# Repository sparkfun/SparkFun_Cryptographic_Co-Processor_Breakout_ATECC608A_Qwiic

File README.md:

SparkFun Cryptographic Co-Processor Breakout - ATECC608A (Qwiic)
========================================

[*SparkFun Cryptographic Co-Processor Breakout - ATECC608A (Qwiic) (DEV-15573)*](https://www.sparkfun.com/products/18077)

The SparkFun ATECC608A Cryptographic Co-processor Breakout allows you to add strong security to your IoT node, edge device, or embedded system. This includes asymmetric authentication, symmetric AES-128 encryption/decryption, and much more. As stated above, the ATECC608A has limited Arduino support and the complete datasheet is under NDA with Microchip.

This breakout board includes two Qwiic ports for plug and play functionality. Utilizing our handy Qwiic system, no soldering is required to connect it to the rest of your system. However, we still have broken out 0.1"-spaced pins in case you prefer to use a breadboard. The ATECC608A chip is capable of many cryptographic processes, including, but not limited to:

* Creating and securely storing unique asymmetric key pairs based on Elliptic Curve Cryptography (FIPS186-3).
* AES-128: Encrypt/Decrypt, Galois Field Multiply for GCM
* Creating and verifying 64-byte digital signatures (from 32-bytes of message data).
* Creating a shared secret key on a public channel via Elliptic Curve Diffie-Hellman Algorithm.
* SHA-256 & HMAC Hash including off-chip context save/restore
* Internal high quality FIPS random number generator.
* Embedded in the chip is a 10Kb EEPROM array that can be used for storing keys, certificates, data, consumption logging, and security configurations. Access to the sections of memory can then be restricted and the configuration locked to prevent changes. Each ATECC608A Breakout ships with a guaranteed unique 72-bit serial number and includes several security features to prevent physical attacks on the device itself, or logical attacks on the data transmitted between the device.

A summary datasheet for the ATECC608A is available [here](https://cdn.sparkfun.com/assets/d/5/c/c/a/ATECC608A-CryptoAuthentication-Device-Summary-Data-Sheet-DS40001977B.pdf). The full datasheet is under NDA with Microchip. You will need to contact them for access to the entire datasheet. Meanwhile, the ArduinoATECCX08 Library currently only supports the ATECC608A with SAMD21 Arduino boards

Repository Contents
-------------------

* **/Documentation** - Data sheets, additional product information
* **/Hardware** - Eagle design files (.brd, .sch)
* **/Hardware/Production** - Production panel files (.brd)

Documentation
--------------
* **[ArduinoECCX08 Arduino Library](https://github.com/arduino-libraries/ArduinoECCX08)** - Arduino library for the ATECCX08A.
* **[CryptoAuthLib - ](https://github.com/MicrochipTech/cryptoauthlib)** - Microchip CryptoAuthentication Library (includes Python support).

Product Versions
----------------
* [DEV-18077](https://www.sparkfun.com/products/18077)- Initial Release
* [SPX-15838](https://www.sparkfun.com/products/15838)- SparkX Release

License Information
-------------------

This product is _**open source**_! 

Please review the LICENSE.md file for license information. 

If you have any questions or concerns on licensing, please contact technical support through the [SparkFun forum](https://forum.sparkfun.com/index.php).

Please use, reuse, and modify these files as you see fit. Please maintain attribution to SparkFun Electronics and release any derivative under the same license.

Distributed as-is; no warranty is given.

- Your friends at SparkFun.

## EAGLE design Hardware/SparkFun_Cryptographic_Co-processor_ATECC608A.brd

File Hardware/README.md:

SparkFun <PRODUCT NAME> Design Files
=====================================

The .sch and .brd files hare are Eagle CAD schematic and PCB design files from SparkFun Electronics.
A freeware version of Eagle can be found [here](https://www.autodesk.com/products/eagle/free-download).

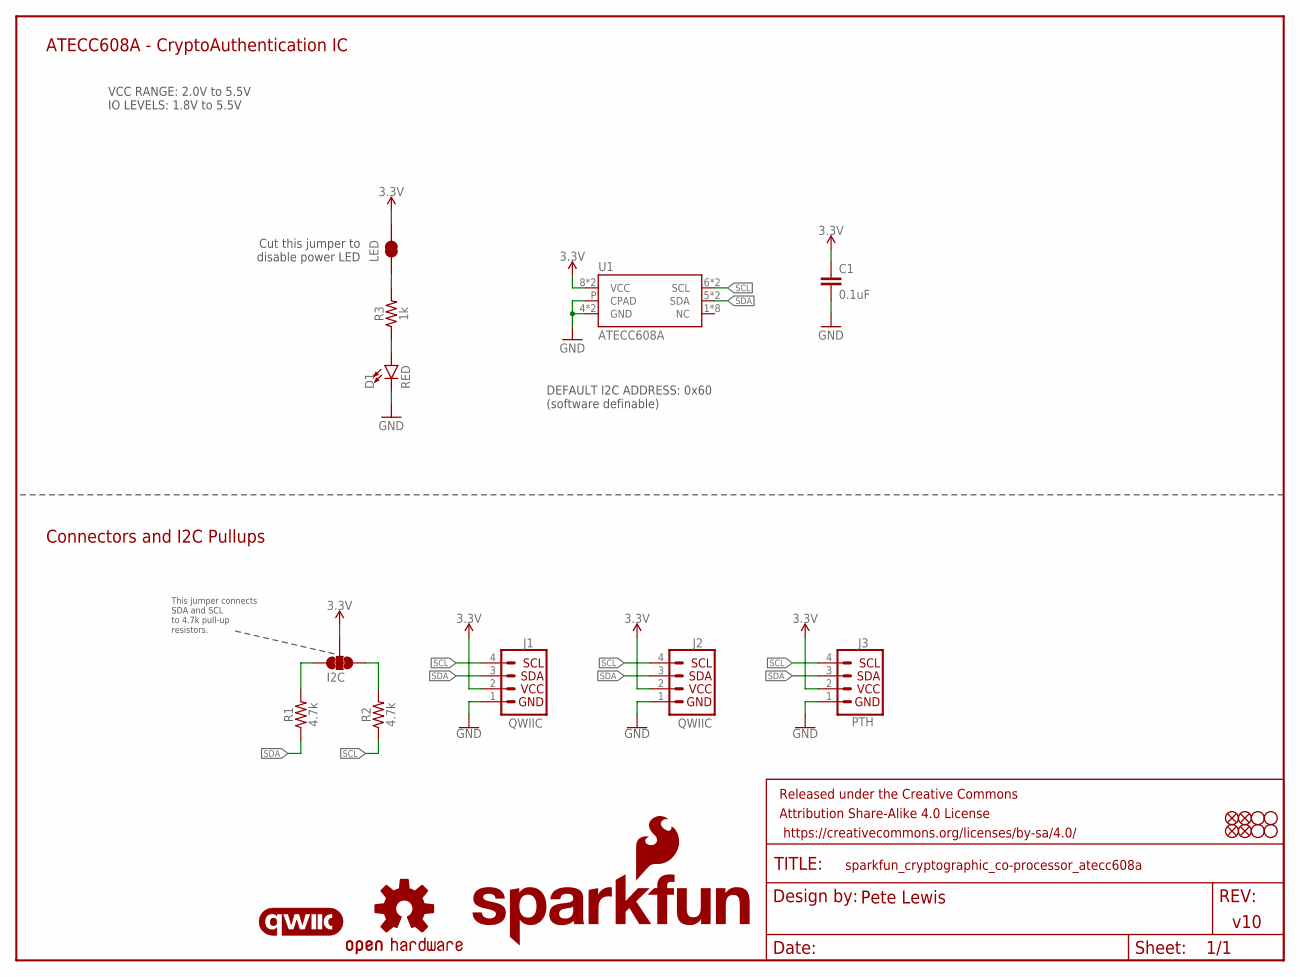
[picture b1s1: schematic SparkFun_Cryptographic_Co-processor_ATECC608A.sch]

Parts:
C1: 0.1uF; 0603
D1: RED; LED-0603
FD1, FD2, FD3, FD4: FIDUCIAL1X2; FIDUCIAL-1X2
FRAME1: FRAME-LETTER; CREATIVE_COMMONS
H1, H2, H3, H4: STAND-OFF
I2C: JUMPER-SMT_3_2-NC_TRACE_SILK; SMT-JUMPER_3_2-NC_TRACE_SILK
J1, J2: QWIIC; JST04_1MM_RA
J3: PTH; 1X04_NO_SILK
LED: JUMPER-SMT_2_NC_TRACE_SILK; SMT-JUMPER_2_NC_TRACE_SILK
LOGO1: SFE_LOGO_NAME_FLAME.1_INCH; SFE_LOGO_NAME_FLAME_.1
LOGO3: QWIIC_LOGO_4MM; QWIIC_4MM
LOGO4: OSHW-LOGOS; OSHW-LOGO-S
R1, R2: 4.7k; 0603
R3: 1k; 0603
U1: ATECC608A; DUAL_UDFN_2X3MM_SOIC-8

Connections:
3.3V: C1.1, I2C.2, J1.2, J2.2, J3.2, LED.2, U1.8 (VCC), U1.8S (VCC)
GND: C1.2, D1.C, J1.1, J2.1, J3.1, U1.4 (GND), U1.4S (GND), U1.P (CPAD)
unnamed: D1.A, R3.1
unnamed: I2C.3, R1.2
unnamed: I2C.1, R2.2
unnamed: LED.1, R3.2
SCL: J1.4, J2.4, J3.4, R2.1, U1.6 (SCL), U1.6S (SCL)
SDA: J1.3, J2.3, J3.3, R1.1, U1.5 (SDA), U1.5S (SDA)

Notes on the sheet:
This jumper connects SDA and SCL to 4.7k pull-up resistors.
v10
Pete Lewis
ATECC608A - CryptoAuthentication IC
VCC RANGE: 2.0V to 5.5V IO LEVELS: 1.8V to 5.5V
Connectors and I2C Pullups
Cut this jumper to disable power LED
DEFAULT I2C ADDRESS: 0x60 (software definable)

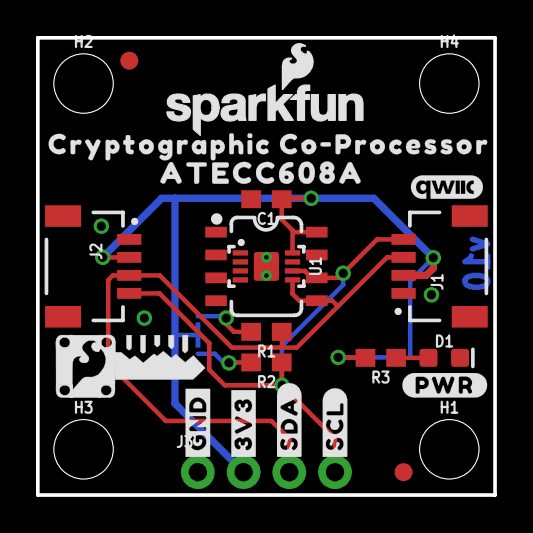
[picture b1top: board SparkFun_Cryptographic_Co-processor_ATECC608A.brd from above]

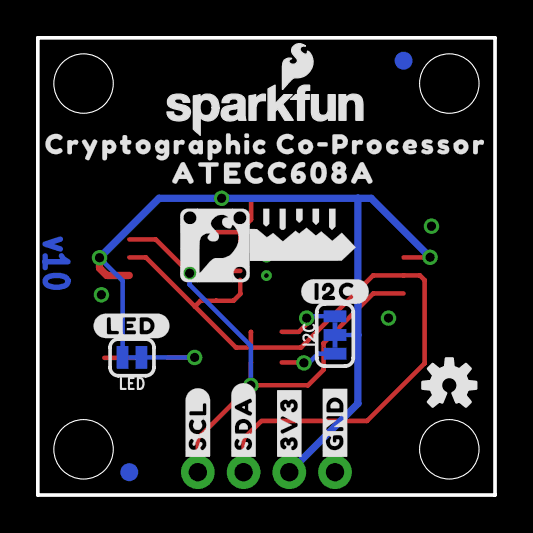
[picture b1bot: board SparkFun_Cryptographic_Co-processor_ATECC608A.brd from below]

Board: 2 copper layers, 25.4 x 25.4 mm, 41 parts (15 on the bottom side), 8 nets.

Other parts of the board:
LOGO2: SFE_LOGO_NAME_FLAME.1_INCH; SFE_LOGO_NAME_FLAME_.1
U$1: #I2C#0
U$2, U$13: #SCL#0
U$3: #LED#0
U$4, U$17: #SDA#0
U$5, U$7: ATECC608A0
U$6, U$20: #3V3#0
U$8: CRYPTO_COPROCESSOR_LOGO_LARGE
U$9, U$19: CRYPTOGRAPHIC_CO#PROCESSOR0
U$10: CRYPTO_COPROCESSOR_LOGO_SMALL
U$14: #PWR#0
U$21, U$23: #GND#0

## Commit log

2021-03-23 Layout done - w/vector logos and buzzards
2021-03-26 eng 1st run checklist stuff
    -added qwiic logo as device so it has logo in SCH
    -update vector font to "non-legacy"
    -cleaned up assembly sheet view attribute placement
    -IC datasheet (summary only)
    -measures updated, PNG and PDF files created.
    -Exported SCH as PDF in docs
2021-03-26 Manufacturing tool color set and preview PNG
2021-03-29 Move to dual-type package (UDFN and SOIC)
2021-03-30 Added PROD_ID to atecc608a (soic-8 package)
    -also added RoHS documentation for the IC.
2021-03-30 PWR to text only buzzard (was previously inverted bubble)
2021-04-08 Production panel BRD and Gerbers (v10)

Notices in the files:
parts and their libraries:
SparkFun-Aesthetics: Licensing: Creative Commons ShareAlike 4.0 International - https://creativecommons.org/licenses/by-sa/4.0
SparkFun-Aesthetics: Released under the Creative Commons Attribution Share-Alike 4.0 License
SparkFun-Aesthetics: https://creativecommons.org/licenses/by-sa/4.0
